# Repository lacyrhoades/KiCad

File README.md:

# schematics
Kicad schematics of components

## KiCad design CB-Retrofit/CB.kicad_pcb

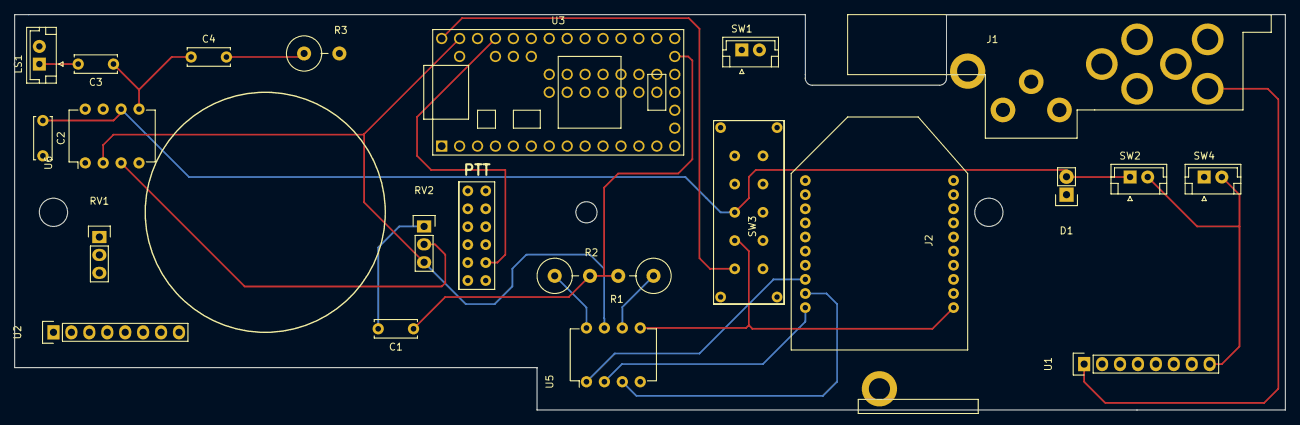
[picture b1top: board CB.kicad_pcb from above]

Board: 2 copper layers, 180.0 x 56.0 mm, 24 parts (0 on the bottom side), 24 nets.

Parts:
C1: CP1; C_Disc_D6.0mm_W2.5mm_P5.00mm
C2: 1µF; C_Disc_D6.0mm_W2.5mm_P5.00mm
C3: 220 µF; C_Disc_D6.0mm_W2.5mm_P5.00mm
C4: C_Small; C_Disc_D6.0mm_W2.5mm_P5.00mm
D1: LED; Pin_Header_Straight_1x02
J1: PowerJack; Power_Jack
J2: POT_MOUNT
LS1: Speaker; JST_EH_B02B-EH-A_02x2.50mm_Straight
R1, R2: 1k; Resistor_Vertical_RM5mm
R3: R_Small; Resistor_Vertical_RM5mm
RV1: 10k LIN; Pin_Header_Straight_1x03
RV2: 10k AUDIO; Pin_Header_Straight_1x03
S1: 4PDT; 4pdt
SW1, SW2: SW_SPST; JST_EH_B02B-EH-A_02x2.50mm_Straight
SW3: 3pdt
SW4: SW_Push; JST_EH_B02B-EH-A_02x2.50mm_Straight
U1: PBOOST500; Pin_Header_Straight_1x08
U2: SD_Card_Module; Pin_Header_Straight_1x08
U3: Teensy3.2; Teensy30_31_32_LC
U4: AUDIOB_I2S; AudioB_I2S
U5: TDA1543; DIP-8_W7.62mm
U6: LM386; DIP-8_W7.62mm

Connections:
+5V: C2.1, D1.2, RV1.1, SW2.1, SW3.3, U6.6
/BT_POW: SW3.2, U4.11, U5.5
/CS: U2.4, U3.12
/DI: U2.7, U3.14
/DO: U2.5, U3.9
/LINE_OUT: C1.1, R1.2, R2.2, U3.19
/PTT: S1.11, U3.30
/SCK: U2.6, U3.21
/TEENSY_POW: SW3.1, U2.3, U3.33
GND: C2.2, D1.1, J1.8, J2.1, J2.2, LS1.2, R3.2, RV1.3, S1.10, SW4.1, U1.2, U1.5, U1.7, U2.1, U2.8, U3.1, U3.39, U4.16, U5.4, U6.4
GNDA: RV2.3, U3.32, U5.7, U6.2
unnamed: C1.2, RV2.1
unnamed: C3.1, C4.1, U6.5
unnamed: C3.2, LS1.1
unnamed: C4.2, R3.1
unnamed: R1.1, U5.6
unnamed: R2.1, U5.8
unnamed: RV1.2, U3.22
unnamed: RV2.2, U6.3
unnamed: SW2.2, SW4.2, U1.8
unnamed: U4.8, U5.1
unnamed: U4.9, U5.3
unnamed: U4.10, U5.2
VCC: J1.7, U1.1

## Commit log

2017-10-21 First two projects' files
2017-10-26 Moved sheets around
2017-11-26 Cleaning up this rescue file bs
2017-11-26 First possible PCB, needs a few more footprints
2017-11-27 Second attempt
